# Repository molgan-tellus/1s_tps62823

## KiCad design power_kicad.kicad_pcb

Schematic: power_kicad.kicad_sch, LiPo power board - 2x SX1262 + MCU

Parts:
C1, C2, C8, C9, C17, C20: 10uF; C_0805_2012Metric
C3, C6, C7, C16, C18, C21: 100nF; C_0603_1608Metric
C4, C5, C10, C14, C15: 22uF; C_0805_2012Metric
C11: 100nF; C_0402_1005Metric
C12: 120pF; C_0603_1608Metric
C13: 470pF DNP; C_0603_1608Metric; not fitted
C19, C22: 100pF; C_0603_1608Metric
D1: SMF5.0A; D_SOD-123F; LCSC C169426
D2, D3: SS34; D_SMA; LCSC C8678
D4: SS54; D_SMA; LCSC C22452
D5: 6.8V zener; D_SMA; LCSC C382952
F1: mSMD200 2A; Fuse_1812_4532Metric; LCSC C5128770
FB1, FB2: 600R@100MHz 3A; L_1206_3216Metric; LCSC C317622
FB3, FB4: 600R@100MHz; L_0805_2012Metric; LCSC C1017
J1: USB-C 5V; USB_C_Receptacle_HRO_TYPE-C-31-M-12; LCSC C165948
J2: LIPO 3000mAh; JST_PH_S2B-PH-K_1x02_P2.00mm_Horizontal; LCSC C173752
J3: SOLCELL <=6V HAL; PinHeader_1x02_P2.54mm_Vertical
J4: RF-HAL: RF1 G RF2 G; PinHeader_1x04_P2.54mm_Vertical
J7: MCU CTRL; PinHeader_1x10_P2.54mm_Vertical
JP1: VSOL-BYGEL; SolderJumper-2_P1.3mm_Open_TrianglePad1.0x1.5mm
L1: 1uH SWPA4030S; L_Sunlord_SWPA4030S; LCSC C42193
LED1: ROD CHRG; LED_0603_1608Metric; LCSC C2286
LED2: GRON STDBY; LED_0603_1608Metric; LCSC C12624
Q1: 8205A; SOT-23-6; LCSC C351449
Q2: AO4407A; SOIC-8_3.9x4.9mm_P1.27mm; LCSC C2841482
Q3, Q5: AO3401A; SOT-23; LCSC C15127
Q4, Q6, Q9: 2N7002; SOT-23; LCSC C8545
Q7: 2N7002DW-7-F; SOT-363_SC-70-6; LCSC C83571
R1, R2: 5.1k; R_0603_1608Metric
R3: 24k; R_0603_1608Metric; LCSC C23352
R4, R7, R21: 1k; R_0603_1608Metric
R5: 10mR 1% 3W; R_2512_6332Metric; LCSC C2903468
R6: 330R; R_0603_1608Metric
R8, R12, R14, R17, R18, R19, R20, R25, R26, R27, R28, R33: 100k; R_0603_1608Metric
R9, R10: 4.7k; R_0603_1608Metric
R11, R30, R31: 10k; R_0603_1608Metric
R13: 22.1k; R_0603_1608Metric
R16: 2R SNUB DNP; R_0603_1608Metric; not fitted
R22: 33k; R_0603_1608Metric; LCSC C4216
R23: 8.2k; R_0603_1608Metric; LCSC C25981
R24: 2.2k; R_0603_1608Metric; LCSC C4190
R29, R32: 150k; R_0603_1608Metric; LCSC C22807
TP1: MP0; TestPoint_Pad_D1.0mm
TP2: MP1; TestPoint_Pad_D1.0mm
TP3: MP2; TestPoint_Pad_D1.0mm
TP4: EN_RF1; TestPoint_Pad_D1.0mm
TP5: EN_RF2; TestPoint_Pad_D1.0mm
TP6: BUCK_EN; TestPoint_Pad_D1.0mm
TP7: PROG; TestPoint_Pad_D1.0mm
TP8: VBS; TestPoint_Pad_D1.0mm
TP9: VSOL; TestPoint_Pad_D1.0mm
TP10: SYS; TestPoint_Pad_D1.0mm
TP11: GND; TestPoint_Pad_D1.0mm
U2: TP4056; SOIC-8-1EP_3.9x4.9mm_P1.27mm_EP2.29x3mm; LCSC C16581
U3: DW01A; SOT-23-6; LCSC C351410
U4: INA226; VSSOP-10_3x3mm_P0.5mm; LCSC C49851
U5: HT7833-A; SOT-89-3; LCSC C347195
U6: TPS62823DLCR; VSON-8_1.5x2mm_P0.5mm; LCSC C2693497
U7: TCA6408ARGTR; VQFN-16-1EP_3x3mm_P0.5mm_EP1.68x1.68mm; LCSC C181499

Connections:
3V3: C12.1, C14.1, C15.1, C16.1, J7.1, L1.2, Q3.2 (S), Q5.2 (S), R12.1, R17.1, R19.1
3V3_MCU: C6.1, C7.1, C9.1, J7.3, R9.1, R10.1, R11.1, R30.1, R31.1, U4.6 (VS), U5.3 (VOUT), U7.14 (VCCP), U7.15 (VCCI)
3V3_RF1: C17.1, C18.1, C19.1, FB3.2, J4.1
3V3_RF2: C20.1, C21.1, C22.1, FB4.2, J4.3
ALERT: J7.7, R11.2, U4.3 (ALERT)
BAT_P: C2.1, Q2.5 (D), Q2.6 (D), Q2.7 (D), Q2.8 (D), R5.2, U2.5 (BAT), U4.9 (IN-)
BUCK_EN: R14.1, TP6.1, U6.1 (EN), U7.8 (P5)
CC1: J1.A5 (CC1), R1.1
CC2: J1.B5 (CC2), R2.1
CELL_N: C3.2, J2.2, Q1.1 (S1), U3.6 (GND)
CELL_P: J2.1, R5.1, R6.1, U4.8 (VBUS), U4.10 (IN+)
CHG_VIN: C1.1, D2.1 (K), D3.1 (K), LED1.2 (A), LED2.2 (A), R32.1, U2.4 (VCC), U2.8 (CE)
CHRG: R4.2, U2.7 (CHRG)
DD: Q1.2 (D), Q1.5 (D)
DW_VCC: C3.1, R6.2, U3.5 (VCC)
EN_RF1: Q4.1 (G), R18.1, TP4.1, U7.5 (P3)
EN_RF2: Q6.1 (G), R20.1, TP5.1, U7.7 (P4)
FB_BK: C12.2, R12.2, R13.1, U6.2 (FB)
G1: Q1.6 (G1), U3.1 (OD)
G2: Q1.4 (G2), U3.3 (OC)
GND: C1.2, C2.2, C4.2, C5.2, C6.2, C7.2, C8.2, C9.2, C10.2, C11.2, C13.2, C14.2, C15.2, C16.2, C17.2, C18.2, C19.2, C20.2, C21.2, C22.2, D1.2 (A), D5.2 (A), J1.A1 (GND), J1.A12 (GND), J1.B1 (GND), J1.B12 (GND), J1.S1 (SHIELD), J3.2, J4.2, J4.4, J7.2, J7.4, Q1.3 (S2), Q4.2 (S), Q6.2 (S), Q7.1 (S2), Q7.4 (S1), Q9.2 (S), R1.2, R2.2, R3.2, R7.2, R8.2, R13.2, R14.2, R18.2, R20.2, R25.2, R26.2, R27.2, R29.2, R33.2, TP11.1, U2.1 (TEMP), U2.3 (GND), U2.9 (EP), U4.1 (A1), U4.2 (A0), U4.7 (GND), U5.1 (GND), U6.3 (AGND), U6.4 (NC), U6.5 (PGND), U7.6 (GND), U7.10 (P7), U7.16 (ADDR), U7.17 (EP)
G_RF1: Q3.1 (G), Q4.3 (D), R17.2
G_RF2: Q5.1 (G), Q6.3 (D), R19.2
INT_EXP: J7.8, R31.2, U7.11 (INT)
LED1K: LED1.1 (K), R4.1
LED2K: LED2.1 (K), R21.1
MP0: Q7.5 (G1), R25.1, TP1.1, U7.2 (P0)
MP1: Q7.2 (G2), R26.1, TP2.1, U7.3 (P1)
MP2: Q9.1 (G), R27.1, TP3.1, U7.4 (P2)
PGA: Q7.3 (D1), R22.2
PGB: Q7.6 (D2), R23.2
PGC: Q9.3 (D), R24.2
PROG: R3.1, R22.1, R23.1, R24.1, TP7.1, U2.2 (PROG)
RST_EXP: J7.10, R30.2, U7.1 (RESET)
SCL: J7.6, R10.2, U4.5 (SCL), U7.12 (SCL)
SDA: J7.5, R9.2, U4.4 (SDA), U7.13 (SDA)
SNUB: C13.1, R16.2
SOLAR_P: D3.2 (A), D5.1 (K), J3.1
STDBY: R21.2, U2.6 (STDBY)
SW_BK: L1.1, R16.1, U6.6 (SW)
SW_RF1: FB3.1, Q3.3 (D)
SW_RF2: FB4.1, Q5.3 (D)
SYS: C4.1, C5.1, C8.1, D4.1 (K), FB2.1, Q2.1 (S), Q2.2 (S), Q2.3 (S), TP10.1, U5.2 (VIN)
VBS: R28.2, R29.1, TP8.1, U7.9 (P6)
VBUS: D1.1 (K), D2.2 (A), D4.2 (A), FB1.2, Q2.4 (G), R8.1, R28.1
VBUS_F: F1.2, FB1.1
VBUS_RAW: F1.1, J1.A4 (VBUS), J1.A9 (VBUS), J1.B4 (VBUS), J1.B9 (VBUS)
VIN_BK: C10.1, C11.1, FB2.2, U6.7 (VIN)
VM: R7.1, U3.2 (VM)
VSOL: JP1.1, R32.2, R33.1, TP9.1
VSOL_J: J7.9, JP1.2

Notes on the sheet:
USB-C 5V IN + SKYDD
LADDNING TP4056 (USB + SOL)
BATTERI + CELLSKYDD + SHUNT
POWER PATH (USB-PRIORITET, IDEAL-DIOD-BETEENDE)
STROMMATNING INA226 (I2C)
ALLTID-PA LDO 3V3_MCU
BUCK 3V3 3A TPS62823 + AVSTORNING
LASTBRYTARE + PI-FILTER RADIO 1 (SX1262)
LASTBRYTARE + PI-FILTER RADIO 2 (SX1262)
GPIO-EXPANDER TCA6408A (I2C 0x20): MPPT + EN + VBS, VSOL-DELARE
TESTPUNKTER (FRI KOPPAR)
MCU-ANSLUTNING (nRF52840 CONNECT KIT: 3V3 + I2C + IRQ + VSOL)

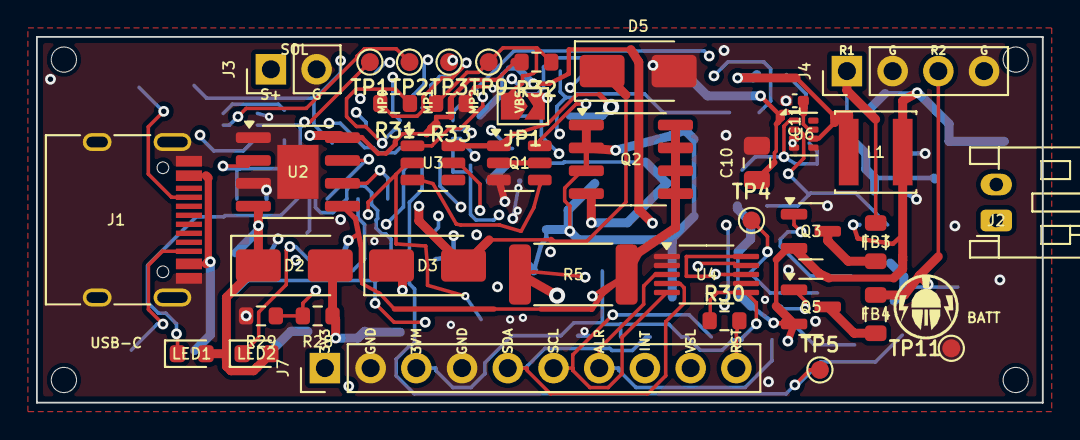
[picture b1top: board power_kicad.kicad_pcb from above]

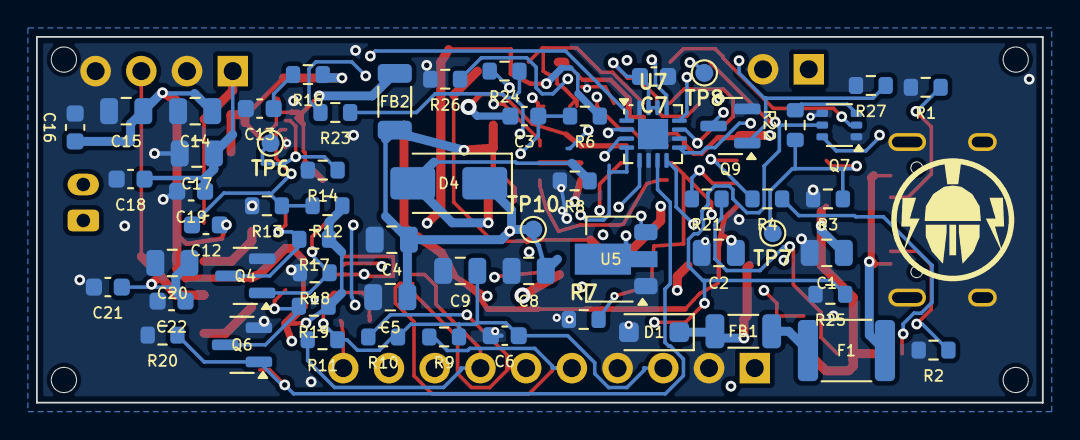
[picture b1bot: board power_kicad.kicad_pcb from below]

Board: 4 copper layers, 55.9 x 20.3 mm, 102 parts (60 on the bottom side), 51 nets.

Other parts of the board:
H1, H2, H3, H4: (no value)

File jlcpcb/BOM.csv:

Comment,Designator,Footprint,LCSC Part #
100nF,C11,C_0402_1005Metric,C1525
120pF,C12,C_0603_1608Metric,C1643
10uF,"C1,C2,C8,C9,C17,C20",C_0805_2012Metric,C15850
100pF,"C19,C22",C_0603_1608Metric,C1635
100nF,"C3,C6,C7,C16,C18,C21",C_0603_1608Metric,C14663
22uF,"C4,C5,C10,C14,C15",C_0805_2012Metric,C45783
SMF5.0A,D1,D_SOD-123F,C169426
SS54,D4,D_SMA,C22452
6.8V zener,D5,D_SMA,C382952
SS34,"D2,D3",D_SMA,C8678
mSMD200 2A,F1,Fuse_1812_4532Metric,C5128770
600R@100MHz 3A,"FB1,FB2",L_1206_3216Metric,C317622
600R@100MHz,"FB3,FB4",L_0805_2012Metric,C1017
USB-C 5V,J1,USB_C_Receptacle_HRO_TYPE-C-31-M-12,C165948
LIPO 3000mAh,J2,JST_PH_S2B-PH-K_1x02_P2.00mm_Horizontal,C173752
1uH SWPA4030S,L1,L_Sunlord_SWPA4030S,C42193
ROD CHRG,LED1,LED_0603_1608Metric,C2286
GRON STDBY,LED2,LED_0603_1608Metric,C12624
8205A,Q1,SOT-23-6,C351449
AO4407A,Q2,SOIC-8_3.9x4.9mm_P1.27mm,C2841482
2N7002DW-7-F,Q7,SOT-363_SC-70-6,C83571
AO3401A,"Q3,Q5",SOT-23,C15127
2N7002,"Q4,Q6,Q9",SOT-23,C8545
24k,R3,R_0603_1608Metric,C23352
10mR 1% 3W,R5,R_2512_6332Metric,C2903468
330R,R6,R_0603_1608Metric,C23138
22.1k,R13,R_0603_1608Metric,C25961
33k,R22,R_0603_1608Metric,C4216
8.2k,R23,R_0603_1608Metric,C25981
2.2k,R24,R_0603_1608Metric,C4190
5.1k,"R1,R2",R_0603_1608Metric,C23186
10k,"R11,R30,R31",R_0603_1608Metric,C25804
150k,"R29,R32",R_0603_1608Metric,C22807
1k,"R4,R7,R21",R_0603_1608Metric,C21190
100k,"R8,R12,R14,R17,R18,R19,R20,R25,R26,R27,R28,R33",R_0603_1608Metric,C25803
4.7k,"R9,R10",R_0603_1608Metric,C23162
TP4056,U2,SOIC-8-1EP_3.9x4.9mm_P1.27mm_EP2.29x3mm,C16581
DW01A,U3,SOT-23-6,C351410
INA226,U4,VSSOP-10_3x3mm_P0.5mm,C49851
HT7833-A,U5,SOT-89-3,C347195
TPS62823DLCR,U6,VSON-8_1.5x2mm_P0.5mm,C2693497
TCA6408ARGTR,U7,VQFN-16-1EP_3x3mm_P0.5mm_EP1.68x1.68mm,C181499
